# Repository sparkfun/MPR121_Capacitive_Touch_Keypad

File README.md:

**NOTE:** *This product has been retired from our catalog. If you are looking for more up-to-date info, please check out some of these resources to see how other users are still hacking and improving on this product.*
* *[SparkFun Forum](https://forum.sparkfun.com/)*
* *[Comments Here on GitHub](https://github.com/sparkfun/MPR121_Capacitive_Touch_Keypad/issues)*
* *[IRC Channel](https://www.sparkfun.com/news/263)*

MPR121 Capacitive Touch Keypad
==============================

[MPR121 Capacitive Touch Keypad (SEN-12017)](https://www.sparkfun.com/products/12017)

The MPR121 capacitive keypad uses the MPR121 and 12 touch sensitive pads to give you a simple 'keypad' with an I2C output. The board 
also has four mounting holes allowing it to be used as na input system in place of traditional buttons. 

Note: This is uses 3.3V logic. You will want to use a logic level converter with this for 5V systems. 

Repository Contents
-------------------
* **/Firmware** - Any firmware that the part ships with, 
* **/Hardware** - All Eagle design files (.brd, .sch)
* **/Production** - Test bed files and production panel files

Documentation
--------------
* **[Hookup Guide](https://learn.sparkfun.com/tutorials/mpr121-hookup-guide)** - Basic hookup guide for the MPR121.

Version History
---------------
* [SEN-10250](https://www.sparkfun.com/products/10250) Version 1.3

License Information
-------------------
The hardware is released under [Creative Commons Share-alike 3.0](http://creativecommons.org/licenses/by-sa/3.0/).  
All other code is open source so please feel free to do anything you want with it; you buy me a beer if you use this and we meet someday ([Beerware license](http://en.wikipedia.org/wiki/Beerware)).

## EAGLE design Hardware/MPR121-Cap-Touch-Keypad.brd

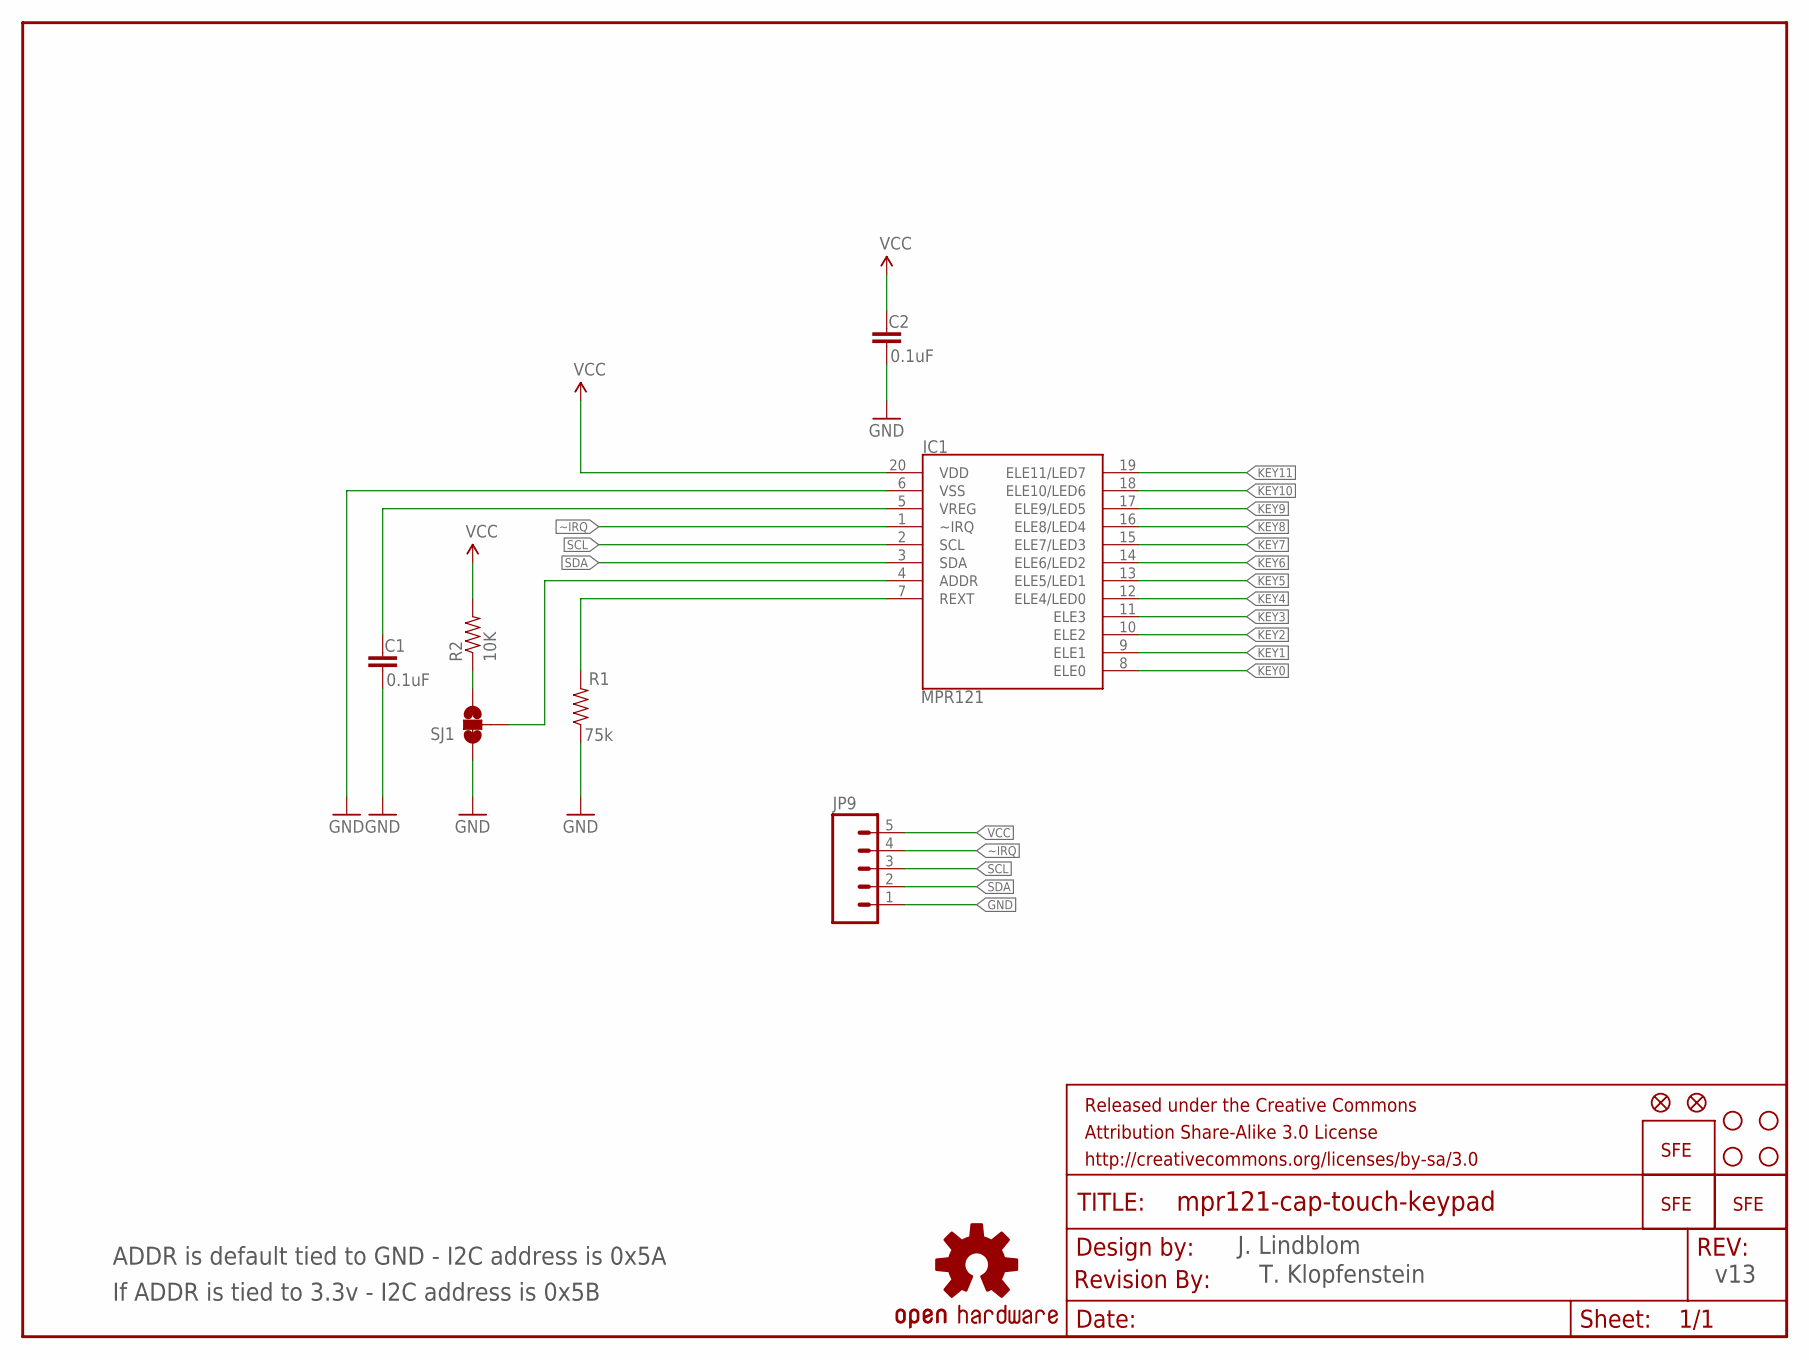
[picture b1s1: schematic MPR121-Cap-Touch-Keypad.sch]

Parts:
C1, C2: 0.1uF; 0603-CAP
FRAME1: FRAME-LETTER; CREATIVE_COMMONS
IC1: MPR121; QFN-20-0.4MM-V2
JP1: LOGO-SFENEW; SFE-NEW-WEBLOGO
JP2, JP6: LOGO-SFESK; SFE-LOGO-FLAME
JP3, JP4, JP7, JP8: STAND-OFF
JP5, JP10: FIDUCIAL1X2; FIDUCIAL-1X2
JP9: M05PTH; 1X05
LOGO1: OSHW-LOGOL; OSHW-LOGO-L
R1: 75k; 0603-RES
R2: 10K; 0603-RES
SJ1: SOLDERJUMPER_2WAYPASTE1&2; SJ_3_PASTE1&2
U$1: REVISION

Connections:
GND: C1.2, C2.2, IC1.6 (VSS), JP9.1, R1.1, SJ1.1
KEY0: IC1.8 (ELE0)
KEY1: IC1.9 (ELE1)
KEY2: IC1.10 (ELE2)
KEY3: IC1.11 (ELE3)
KEY4: IC1.12 (ELE4/LED0)
KEY5: IC1.13 (ELE5/LED1)
KEY6: IC1.14 (ELE6/LED2)
KEY7: IC1.15 (ELE7/LED3)
KEY8: IC1.16 (ELE8/LED4)
KEY9: IC1.17 (ELE9/LED5)
KEY10: IC1.18 (ELE10/LED6)
KEY11: IC1.19 (ELE11/LED7)
unnamed: IC1.4 (ADDR), SJ1.2
unnamed: R2.1, SJ1.3
REXT: IC1.7 (REXT), R1.2
SCL: IC1.2 (SCL), JP9.3
SDA: IC1.3 (SDA), JP9.2
VCC: C2.1, IC1.20 (VDD), JP9.5, R2.2
VREG: C1.1, IC1.5 (VREG)
~IRQ: IC1.1 (~IRQ), JP9.4

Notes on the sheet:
ADDR is default tied to GND - I2C address is 0x5A
v13
J. Lindblom
T. Klopfenstein
If ADDR is tied to 3.3v - I2C address is 0x5B

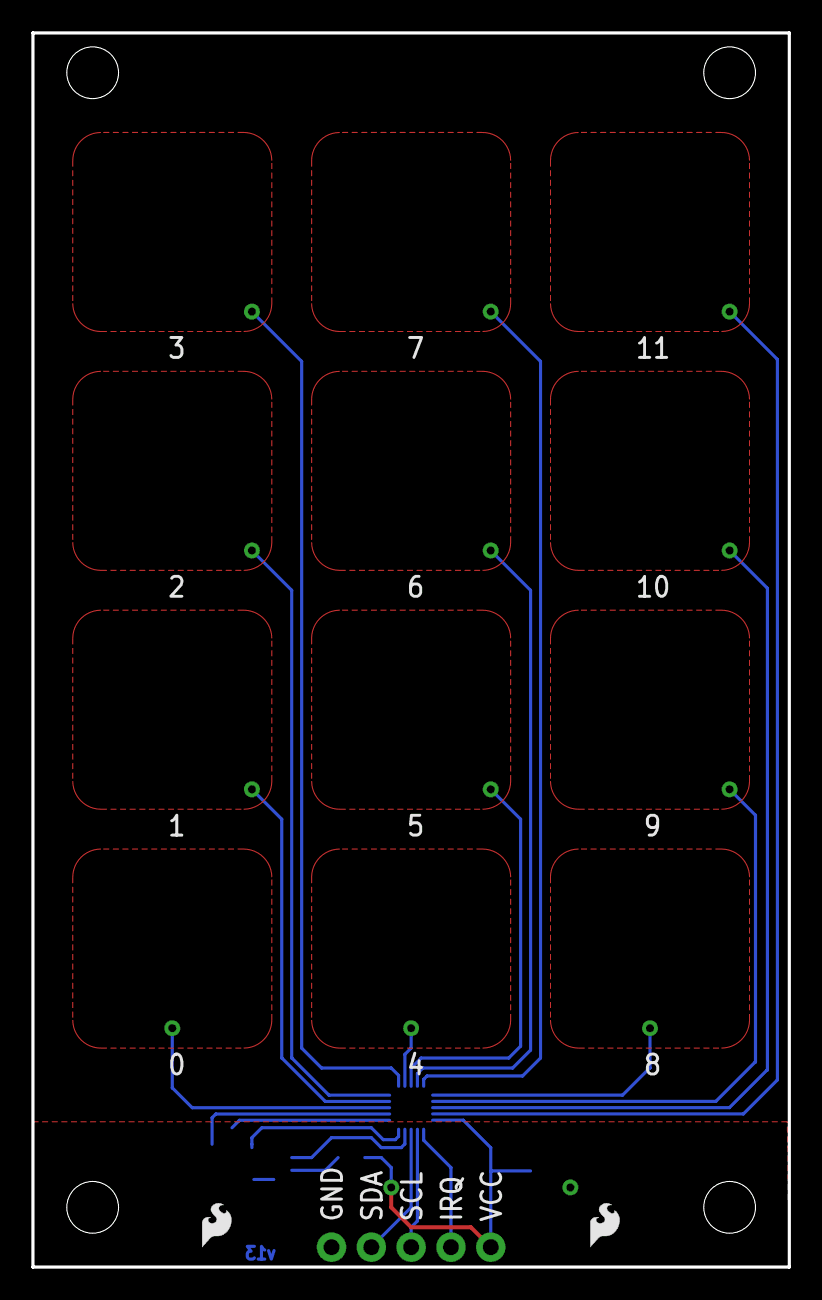
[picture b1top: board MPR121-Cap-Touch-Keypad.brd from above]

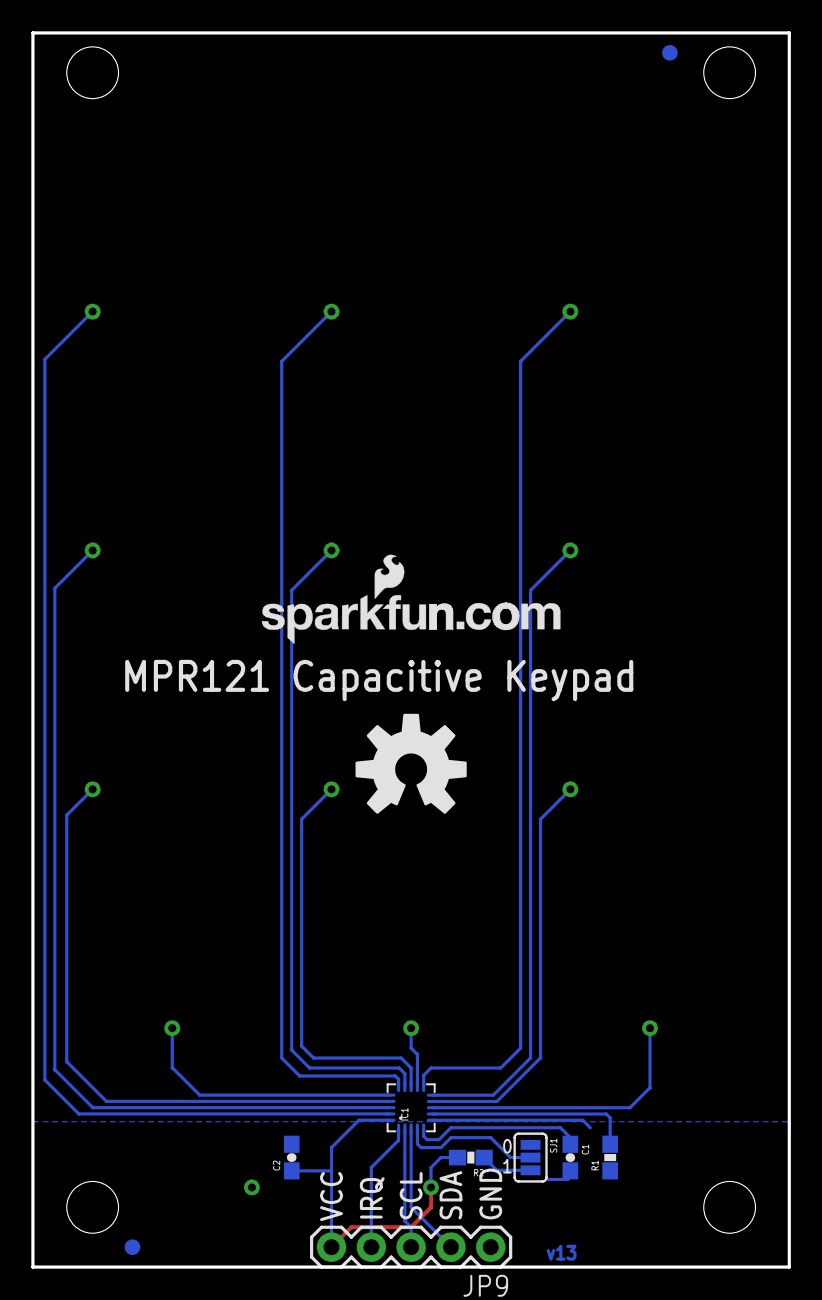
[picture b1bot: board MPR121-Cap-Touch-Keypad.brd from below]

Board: 2 copper layers, 48.3 x 78.7 mm, 19 parts (15 on the bottom side), 9 nets.

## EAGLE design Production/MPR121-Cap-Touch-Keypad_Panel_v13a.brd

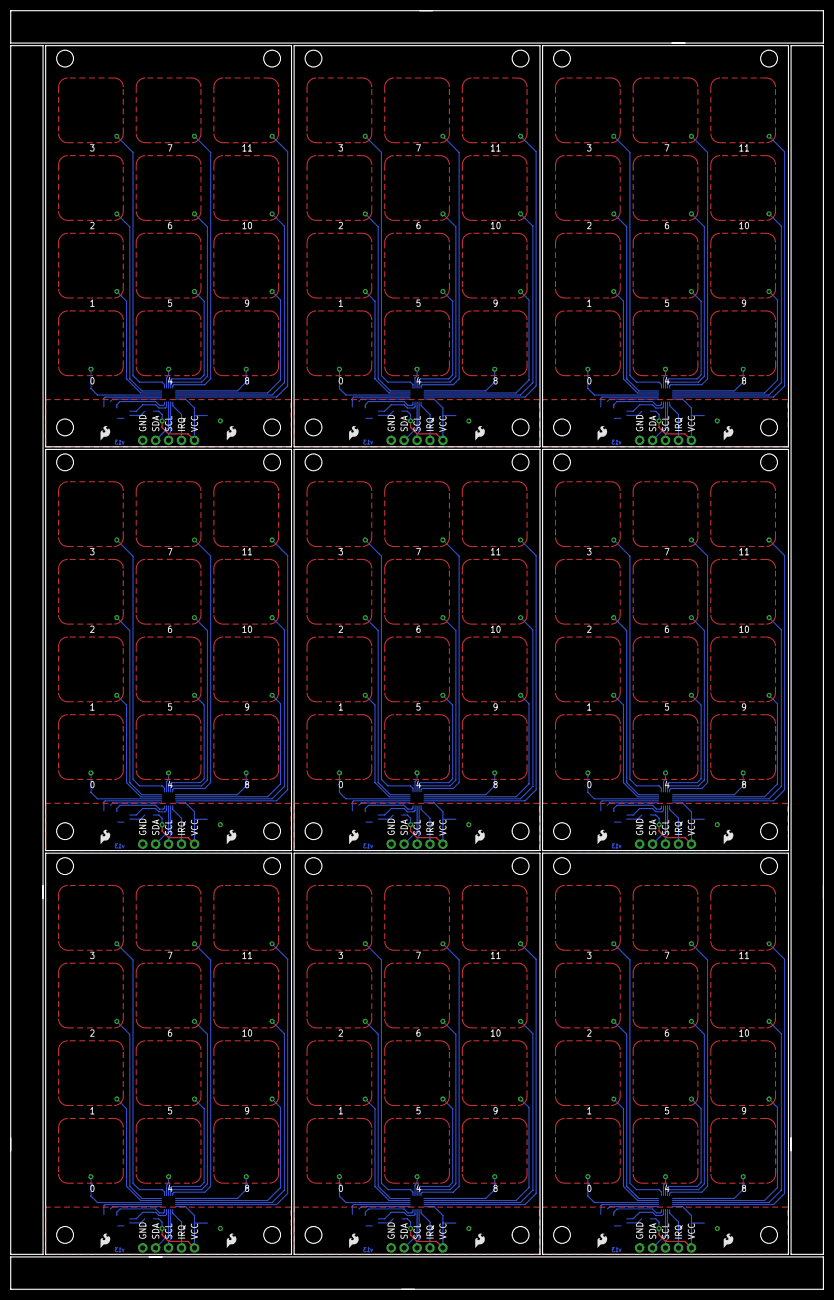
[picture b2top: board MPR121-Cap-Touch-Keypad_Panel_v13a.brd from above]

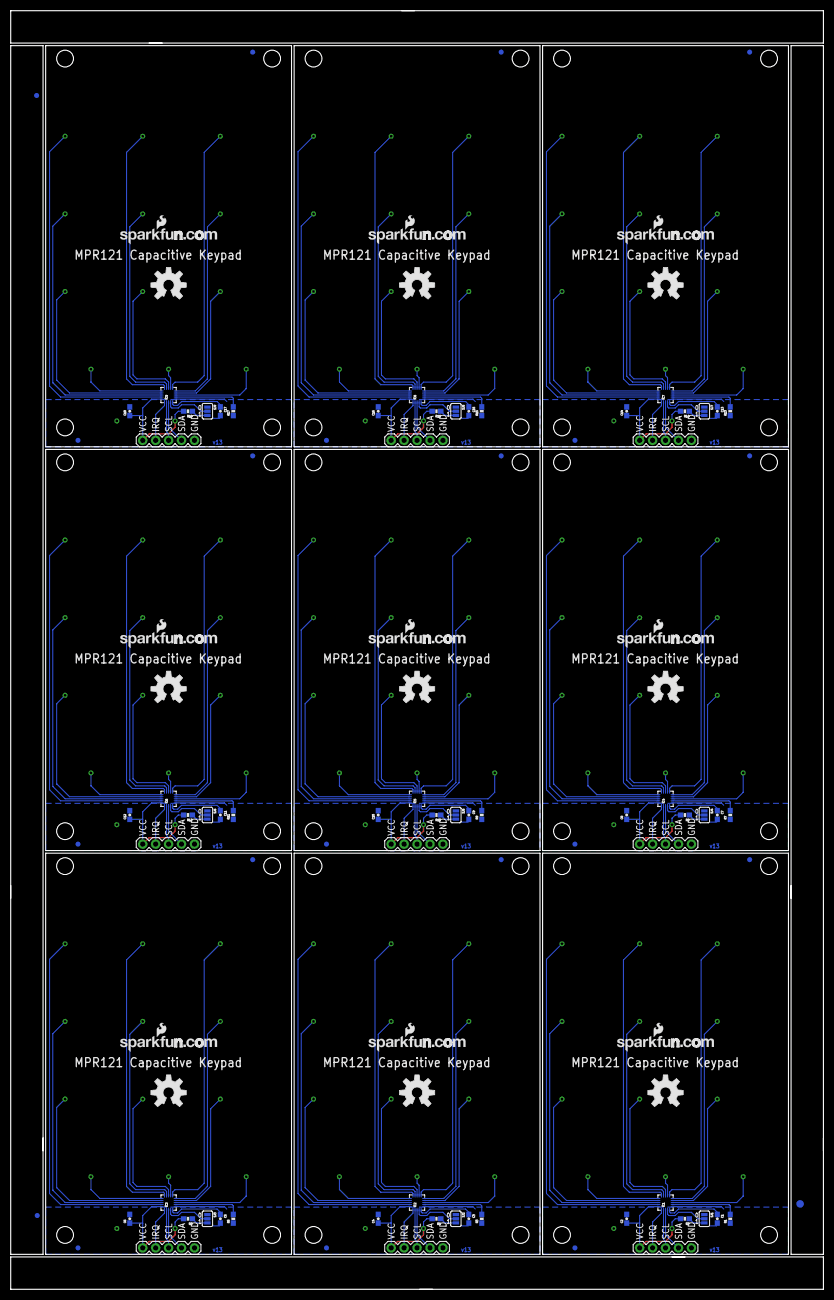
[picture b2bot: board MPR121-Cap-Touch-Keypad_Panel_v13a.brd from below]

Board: 2 copper layers, 159.5 x 251.0 mm, 156 parts (138 on the bottom side), 81 nets.

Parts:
C1, C2, C3, C4, C5, C6, C7, C8, C9, C10, C11, C12, C13, C14, C15, C16, C17, C18: 0.1uF; 0603-CAP
E$1, E$7: FIDUCIAL-1X2
E$2: FIDUCIAL-1.5X3
IC1, IC2, IC3, IC4, IC5, IC6, IC7, IC8, IC9: MPR121; QFN-20-0.4MM-V2
JP1, JP11, JP21, JP31, JP41, JP51, JP61, JP71, JP81: LOGO-SFENEW; SFE-NEW-WEBLOGO
JP2, JP6, JP14, JP15, JP24, JP25, JP34, JP35, JP44, JP45, JP54, JP55, JP64, JP65, JP74, JP75, JP84, JP85: LOGO-SFESK; SFE-LOGO-FLAME
JP3, JP4, JP7, JP8, JP12, JP13, JP16, JP17, JP22, JP23, JP26, JP27, JP32, JP33, JP36, JP37, JP42, JP43, JP46, JP47, JP52, JP53, JP56, JP57, JP62, JP63, JP66, JP67, JP72, JP73, JP76, JP77, JP82, JP83, JP86, JP87: STAND-OFF
JP5, JP10, JP19, JP20, JP29, JP30, JP39, JP40, JP49, JP50, JP59, JP60, JP69, JP70, JP79, JP80, JP89, JP90: FIDUCIAL1X2; FIDUCIAL-1X2
JP9, JP18, JP28, JP38, JP48, JP58, JP68, JP78, JP88: 1X05
LOGO1, LOGO2, LOGO3, LOGO4, LOGO5, LOGO6, LOGO7, LOGO8, LOGO9: OSHW-LOGOL; OSHW-LOGO-L
R1, R3, R5, R7, R9, R11, R13, R15, R17: 75k; 0603-RES
R2, R4, R6, R8, R10, R12, R14, R16, R18: 10K; 0603-RES
SJ1, SJ2, SJ3, SJ4, SJ5, SJ6, SJ7, SJ8, SJ9: SJ_3_PASTE1&2

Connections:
GND: C1.2, C2.2, IC1.6, JP9.1, R1.1, SJ1.1
GND1: C3.2, C4.2, IC2.6, JP18.1, R3.1, SJ2.1
GND2: C5.2, C6.2, IC3.6, JP28.1, R5.1, SJ3.1
GND3: C7.2, C8.2, IC4.6, JP38.1, R7.1, SJ4.1
GND4: C9.2, C10.2, IC5.6, JP48.1, R9.1, SJ5.1
GND5: C11.2, C12.2, IC6.6, JP58.1, R11.1, SJ6.1
GND6: C13.2, C14.2, IC7.6, JP68.1, R13.1, SJ7.1
GND7: C15.2, C16.2, IC8.6, JP78.1, R15.1, SJ8.1
GND8: C17.2, C18.2, IC9.6, JP88.1, R17.1, SJ9.1
unnamed: IC1.4, SJ1.2
unnamed: R2.1, SJ1.3
unnamed: IC2.4, SJ2.2
unnamed: R4.1, SJ2.3
unnamed: IC3.4, SJ3.2
unnamed: R6.1, SJ3.3
unnamed: IC4.4, SJ4.2
unnamed: R8.1, SJ4.3
unnamed: IC5.4, SJ5.2
unnamed: R10.1, SJ5.3
unnamed: IC6.4, SJ6.2
unnamed: R12.1, SJ6.3
unnamed: IC7.4, SJ7.2
unnamed: R14.1, SJ7.3
unnamed: IC8.4, SJ8.2
unnamed: R16.1, SJ8.3
unnamed: IC9.4, SJ9.2
unnamed: R18.1, SJ9.3
REXT: IC1.7, R1.2
REXT1: IC2.7, R3.2
REXT2: IC3.7, R5.2
REXT3: IC4.7, R7.2
REXT4: IC5.7, R9.2
REXT5: IC6.7, R11.2
REXT6: IC7.7, R13.2
REXT7: IC8.7, R15.2
REXT8: IC9.7, R17.2
SCL: IC1.2, JP9.3
SCL1: IC2.2, JP18.3
SCL2: IC3.2, JP28.3
SCL3: IC4.2, JP38.3
SCL4: IC5.2, JP48.3
SCL5: IC6.2, JP58.3
SCL6: IC7.2, JP68.3
SCL7: IC8.2, JP78.3
SCL8: IC9.2, JP88.3
SDA: IC1.3, JP9.2
SDA1: IC2.3, JP18.2
SDA2: IC3.3, JP28.2
SDA3: IC4.3, JP38.2
SDA4: IC5.3, JP48.2
SDA5: IC6.3, JP58.2
SDA6: IC7.3, JP68.2
SDA7: IC8.3, JP78.2
SDA8: IC9.3, JP88.2
VCC: C2.1, IC1.20, JP9.5, R2.2
VCC1: C4.1, IC2.20, JP18.5, R4.2
VCC2: C6.1, IC3.20, JP28.5, R6.2
VCC3: C8.1, IC4.20, JP38.5, R8.2
VCC4: C10.1, IC5.20, JP48.5, R10.2
VCC5: C12.1, IC6.20, JP58.5, R12.2
VCC6: C14.1, IC7.20, JP68.5, R14.2
VCC7: C16.1, IC8.20, JP78.5, R16.2
VCC8: C18.1, IC9.20, JP88.5, R18.2
VREG: C1.1, IC1.5
VREG1: C3.1, IC2.5
VREG2: C5.1, IC3.5
VREG3: C7.1, IC4.5
VREG4: C9.1, IC5.5
VREG5: C11.1, IC6.5
VREG6: C13.1, IC7.5
VREG7: C15.1, IC8.5
VREG8: C17.1, IC9.5
~IRQ: IC1.1, JP9.4
~IRQ1: IC2.1, JP18.4
~IRQ2: IC3.1, JP28.4
~IRQ3: IC4.1, JP38.4
~IRQ4: IC5.1, JP48.4
~IRQ5: IC6.1, JP58.4
~IRQ6: IC7.1, JP68.4
~IRQ7: IC8.1, JP78.4
~IRQ8: IC9.1, JP88.4

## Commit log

2013-08-08 Adding firmware, updated board files, and gitignore
2013-08-08 Changing packages to Production IDs on caps/res
2013-10-02 Created Panel
    v13 panel
2013-12-17 Updating README with new version information
2015-10-16 created new v13 panel
2015-10-23 moved fids to the bottom

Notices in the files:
parts and their libraries:
SparkFun-Aesthetics: Licensing: CC v3.0 Share-Alike You are welcome to use this library for commercial purposes.
SparkFun-Aesthetics: Released under the Creative Commons Attribution Share-Alike 3.0 License
SparkFun-Aesthetics: Released under the Creative Commons
